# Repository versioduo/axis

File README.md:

# V2 axis
🧭 MIDI Orientation Sensor and Accelerometer

Sends MIDI Control Change messages with Quaternion or Euler orientation data.

## Setup
The device can be mounted at any orientation or angle, the reference frame / axes can be aligned to the current posion and stored in the device. This sequence identifies the Y axis (the axis of rotation between the button clicks) and the Z axis (the gravity at the second step):

- The device, or the body it is mounted on, points upwards / to the sky. A double-click of the the button, the LED turns green.

- The device points forward, the zero position. A single click, the LED turns orange. The axes of the sensor are now aligned and the rotation reset to zero.

- Any single click will set the rotation to zero, but not change the reference frame.

- A long-press double-click will store the calibration in the device, the LED flashes purple.

A long-press triple-click erases the stored data, the LED flashes purple.

## Control Change Mapping
Holding the device button down, suppresses all Control Change messages. The CC numbers can be configured in the Setting section. Pressing the blue button there, sends this single CC message; it can be used to map the CC in the Audio Workstation."

## Visualization
[versioduo.com/axis3d](https://versioduo.com/axis3d/)

# Copying
Anyone can use this public domain work without having to seek authorisation, no one can ever own it.

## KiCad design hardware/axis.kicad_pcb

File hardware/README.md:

# V2 axis
🧭 MIDI Orientation Sensor and Accelerometer

## Schematic
[PDF](axis.pdf)

## Bill Of Materials
[Interactive BOM](https://html-preview.github.io/?url=https://github.com/versioduo/axis/main/hardware/axis-bom.html)

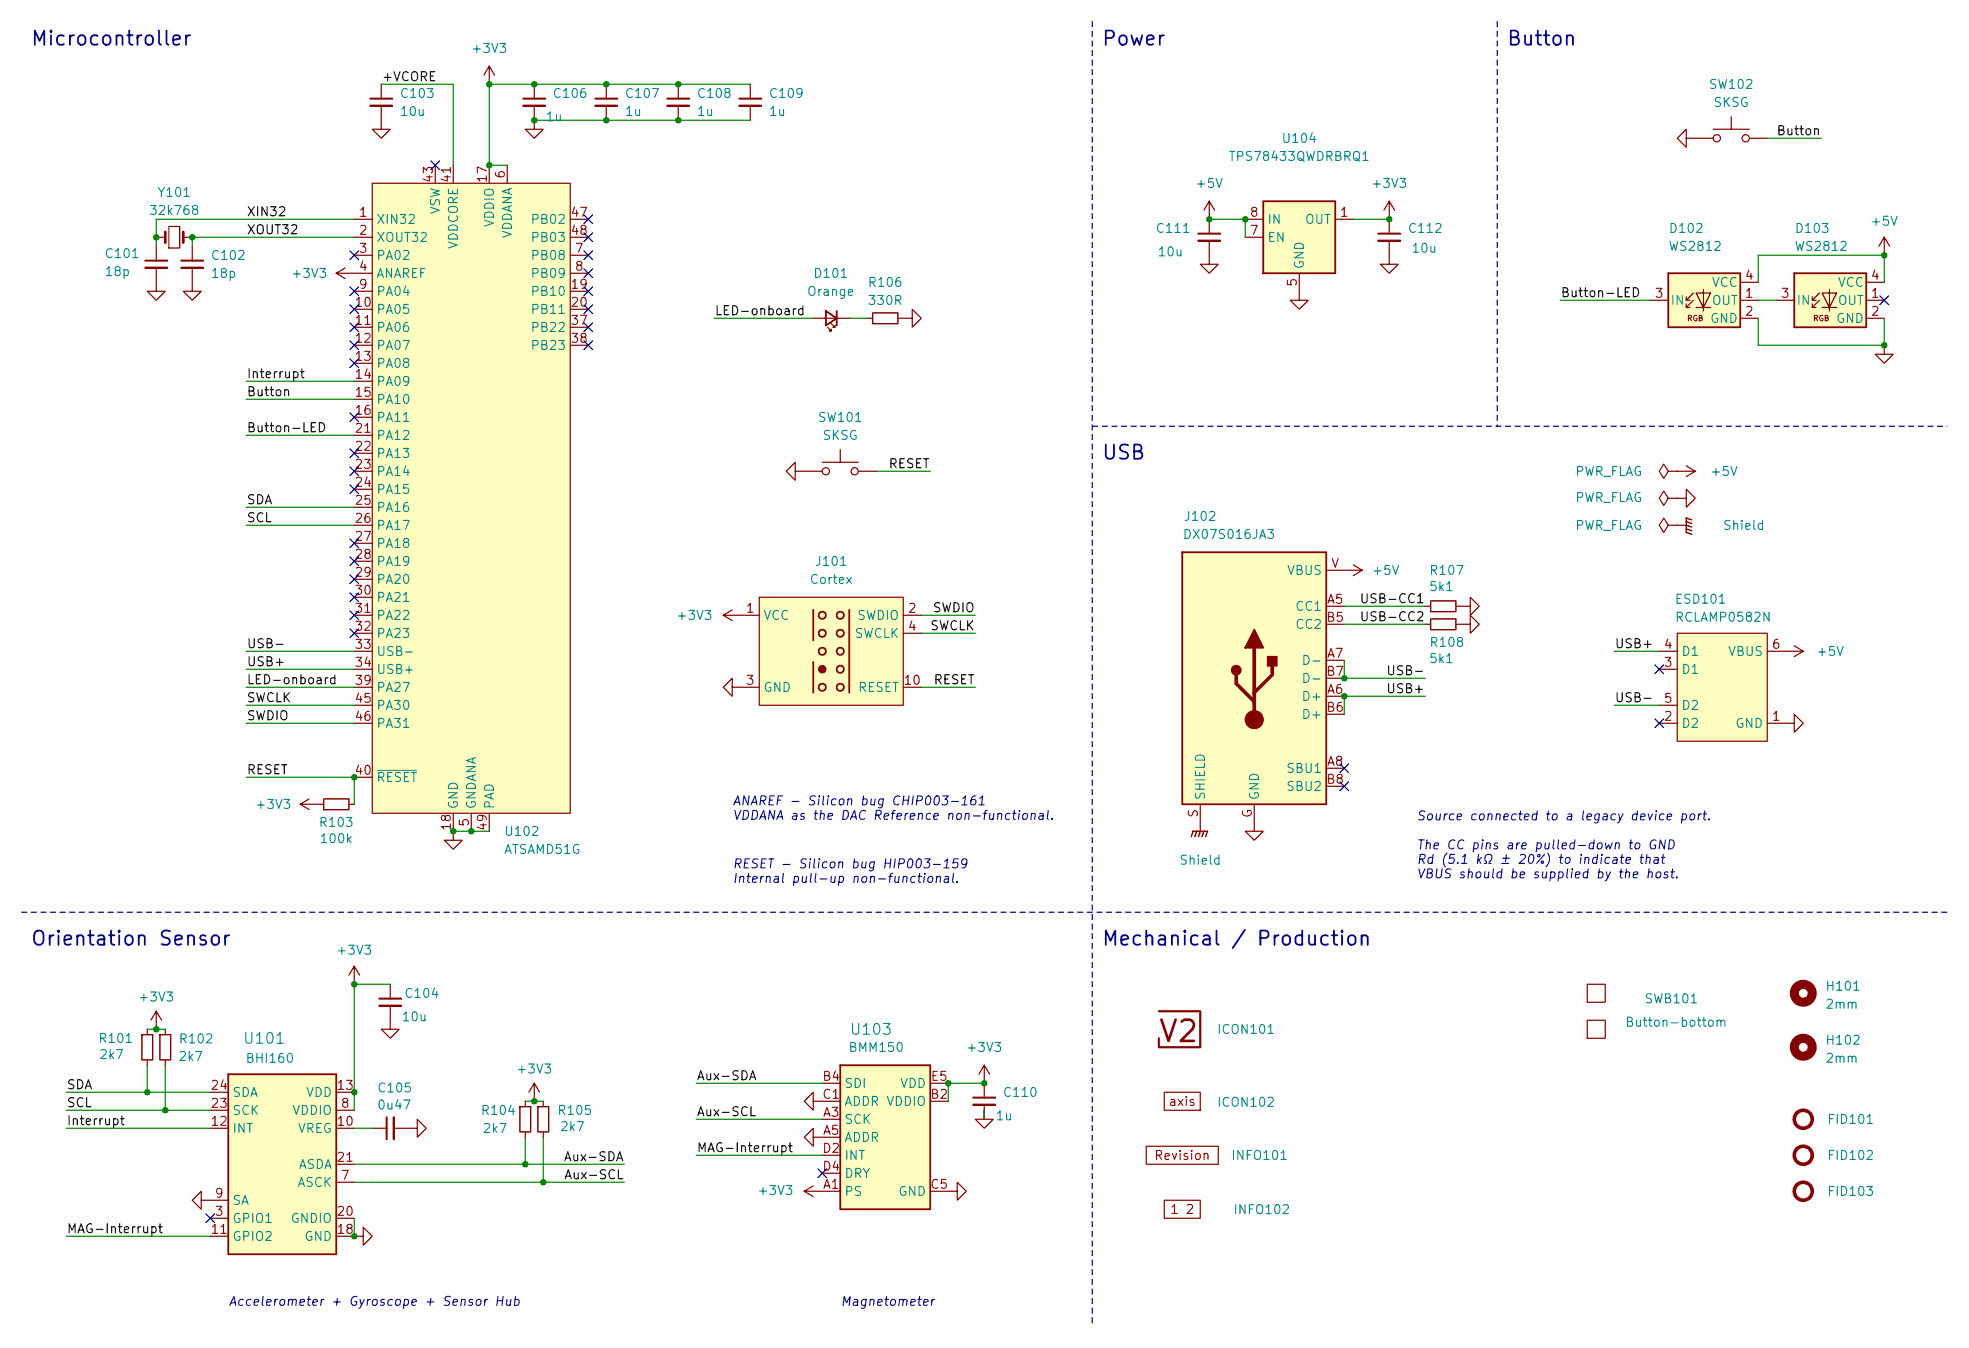
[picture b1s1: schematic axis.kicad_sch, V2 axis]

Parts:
C101, C102: 18p; C_1608; Rating 50V; Mouser 810-CGA3E2C0G1H180J
C103, C104: 10u; C_1608; Rating 10V; Mouser 810-C1608X6S1A106M
C105: 0u47; C_1608; Rating 50V; Mouser 810-CGA3E3X7R1H474KB
C106, C107, C108, C109, C110: 1u; C_1608; Rating 50V; Mouser 810-CGA3E3X7R1H105K0
C111, C112: 10u; C_2012; Rating 25V; Mouser 810-C2012X5R1E106K
D101: Orange; LED_1608; Rating 605nm; Mouser 755-SML-D12D1WT86
D102, D103: WS2812; WS2812-2020; Rating 15mA; LCSC C965555
ESD101: RCLAMP0582N; SLP1210N6; Rating 20kV; Mouser 947-RCLAMP0582N.TCT
FID101, FID102, FID103: Fiducial_Paste; Fiducial_0.5mm_Mask1mm_Paste
H101, H102: 2mm; MountingHole_2mm
ICON101: V2-logo; Logo_Small
ICON102: Board_axis; Board_axis_Small
INFO101: Revision
INFO102: Layer_Numbers-4
J101: Cortex
J102: DX07S016JA3; JAE_DX07S016JA3; Rating USB2.0; Mouser 656-DX07S016JA3R1500
R101, R102, R104, R105: 2k7; R_1608; Rating 100mW; Mouser 71-CRCW06032K70FKEAC
R103: 100k; R_1608; Rating 100mW; Mouser 71-CRCW0603100KFKEAC
R106: 330R; R_1608; Rating 100mW; Mouser 71-CRCW0603330RFKEAC
R107, R108: 5k1; R_1608; Rating 100mW; Mouser 71-CRCW06035K10FKEAC
SW101, SW102: SKSG; Rating 1.6N; Mouser 688-SKSGACE010
SWB101: Button-bottom; PCB_Button-bottom
U101: BHI160; LGA24-3x3; LCSC C464452
U102: ATSAMD51G; QFN-48-1EP_7x7mm_P0.5mm_EP5.45x5.45mm_ThermalVias; Rating Cortex-M4F; Mouser 556-ATSAMD51G19AMU
U103: BMM150; WLCSP-1.56x1.56; LCSC C171681
U104: TPS78433QWDRBRQ1; VSON-8-1_3x3mm_P0.65_EP1.65x2.4mm; Rating 300mA; Mouser 595-TPS78433QWDRBRQ1
Y101: 32k768; Crystal_SMD_3215-2Pin_3.2x1.5mm; Rating 10ppm; Mouser 815-ABS0716632.768KT

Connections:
+3V3: C104.1, C106.1, C107.1, C108.1, C109.1, C110.1, C112.1, J101.1 (VCC), R101.1, R102.1, R103.1, R104.1, R105.1, U101.8 (VDDIO), U101.13 (VDD), U102.4 (ANAREF), U102.6 (VDDANA), U102.17 (VDDIO), U102.36 (VDDIO), U102.44 (VDDIO), U103.A1 (PS), U103.B2 (VDDIO), U103.E5 (VDD), U104.1 (OUT)
+5V: C111.1, D102.4 (VCC), D103.4 (VCC), ESD101.6 (VBUS), J102.V (VBUS), U104.7 (EN), U104.8 (IN)
/+VCORE: C103.1, U102.41 (VDDCORE)
/Aux-SCL: R105.2, U101.7 (ASCK), U103.A3 (SCK)
/Aux-SDA: R104.2, U101.21 (ASDA), U103.B4 (SDI)
/Button: SW102.2, U102.15 (PA10)
/Button-LED: D102.3 (IN), U102.21 (PA12)
/Interrupt: U101.12 (INT), U102.14 (PA09)
/LED-onboard: D101.2 (A), U102.39 (PA27)
/MAG-Interrupt: U101.11 (GPIO2), U103.D2 (INT)
/RESET: J101.10 (RESET), R103.2, SW101.2, U102.40 (~RESET)
/SCL: R102.2, U101.23 (SCK), U102.26 (PA17)
/SDA: R101.2, U101.24 (SDA), U102.25 (PA16)
/SWCLK: J101.4 (SWCLK), U102.45 (PA30)
/SWDIO: J101.2 (SWDIO), U102.46 (PA31)
/Shield: J102.S (SHIELD)
/USB+: ESD101.4 (D1), J102.A6 (D+), J102.B6 (D+), U102.34 (USB+)
/USB-: ESD101.5 (D2), J102.A7 (D-), J102.B7 (D-), U102.33 (USB-)
/USB-CC1: J102.A5 (CC1), R107.1
/USB-CC2: J102.B5 (CC2), R108.1
/XIN32: C101.1, U102.1 (XIN32), Y101.1
/XOUT32: C102.1, U102.2 (XOUT32), Y101.2
GND: C101.2, C102.2, C103.2, C104.2, C105.2, C106.2, C107.2, C108.2, C109.2, C110.2, C111.2, C112.2, D102.2 (GND), D103.2 (GND), ESD101.1 (GND), J101.3 (GND), J101.5 (GND), J102.G (GND), R106.2, R107.2, R108.2, SW101.1, SW102.1, U101.9 (SA), U101.18 (GND), U101.20 (GNDIO), U102.5 (GNDANA), U102.18 (GND), U102.35 (GND), U102.42 (GND), U102.49 (PAD), U103.A5 (ADDR), U103.C1 (ADDR), U103.C5 (GND), U103.E1 (GND), U103.E3 (GND), U104.5 (GND), U104.9 (GND)
unnamed: D101.1 (K), R106.1
unnamed: D102.1 (OUT), D103.3 (IN)
unnamed: C105.1, U101.10 (VREG)

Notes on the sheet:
﻿ANAREF - Silicon bug CHIP003-161 VDDANA as the DAC Reference non-functional.
RESET - ﻿Silicon bug HIP003-159 Internal pull-up non-functional.
﻿Source connected to a legacy device port. The CC pins are pulled-down to GND Rd (5.1 kΩ ± 20%) to indicate that VBUS should be supplied by the host.
Button
Mechanical / Production
Magnetometer
Power
Accelerometer + Gyroscope + Sensor Hub
Microcontroller
USB
Orientation Sensor

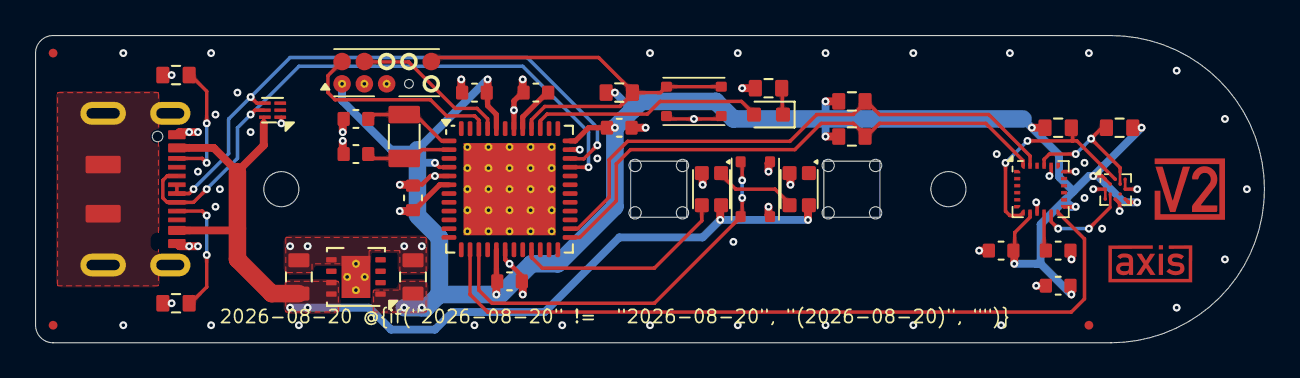
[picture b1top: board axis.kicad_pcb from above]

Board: 4 copper layers, 70.0 x 17.5 mm, 43 parts (0 on the bottom side), 25 nets.

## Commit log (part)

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2021-09-24 Import
2025-11-19 Add gyroscope
2025-11-20 Add help text
2026-01-14 Update parts
2026-01-19 Refresh
2026-02-01 Update library
2026-02-05 Update I2C
2026-02-10 Use date as revision
2026-02-13 Replace Order_Number
2026-02-25 Export stencil
2026-03-14 Update ESD suppressor
2026-03-21 KiCad 10
2026-04-24 Update DRC
2026-05-11 Good Bye Imperial
2026-06-23 Update V2MIDI API
